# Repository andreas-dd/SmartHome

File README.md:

# SmartHome

## [HB-UNI-Sen-CAP-MOIST-Complete](HB-UNI-Sen-CAP-MOIST-Complete)
Ein kompakter Bodenfeuchtesensor komplett auf einer einzigen Platine inkl. kleinem Gehäuse.

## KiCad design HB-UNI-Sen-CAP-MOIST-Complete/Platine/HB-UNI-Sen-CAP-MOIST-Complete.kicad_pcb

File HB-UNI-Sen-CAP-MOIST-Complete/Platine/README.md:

# Platine und Schaltung

Hier findet sich das KiCad Projekt.
Die Batteriekontakte sind [Keystone Electronics 92](https://www.conrad.de/de/p/keystone-electronics-92-einzelkontakt-1x-mignon-aa-a-cr-2-durchsteckmontage-tht-b-x-h-12-mm-x-15-mm-651036.html).
Das Funkmodem ist ein Modul von [EByte](https://www.amazon.de/dp/B0BRZTSYPM?ref=ppx_yo2ov_dt_b_fed_asin_title&th=1).
Es kann ein zusätzlicher kapazitiver Sensor angeschlossen werden, ist im Sketch aber auskommentiert. Ebenfalls kann der Temperatursensor entfallen, dafür muss im Sketch in Zeile 15
```
   #define NO_DS18B20 
```
aktiviert werden.

## Bestückung
Beim ersten Exemplar habe ich nacheinander den Spannungsregler, dann den integrierten Sensor bestückt und geprüft. Danach den Prozessor verlötet sowie Fuses und Firmware programmiert. Zum Schluss das Funkmodem auflöten. Die nachfolgenden Platinen sind auf einen Rutsch mit Lötpaste und Heißluft bestückt worden, das Funkmodem nur an den markierten Kontakten mit dem Lötkolben. 

Die Antenne nicht vergessen, dafür einen 83mm langen Draht auf der Batterieseite bestücken und durch die [Antennenhalter](../Gehaeuse) fädeln:

# Schaltplan
der Schaltplan ist als [PDF verfügbar](HB-UNI-Sen-CAP-MOIST-Complete.pdf)

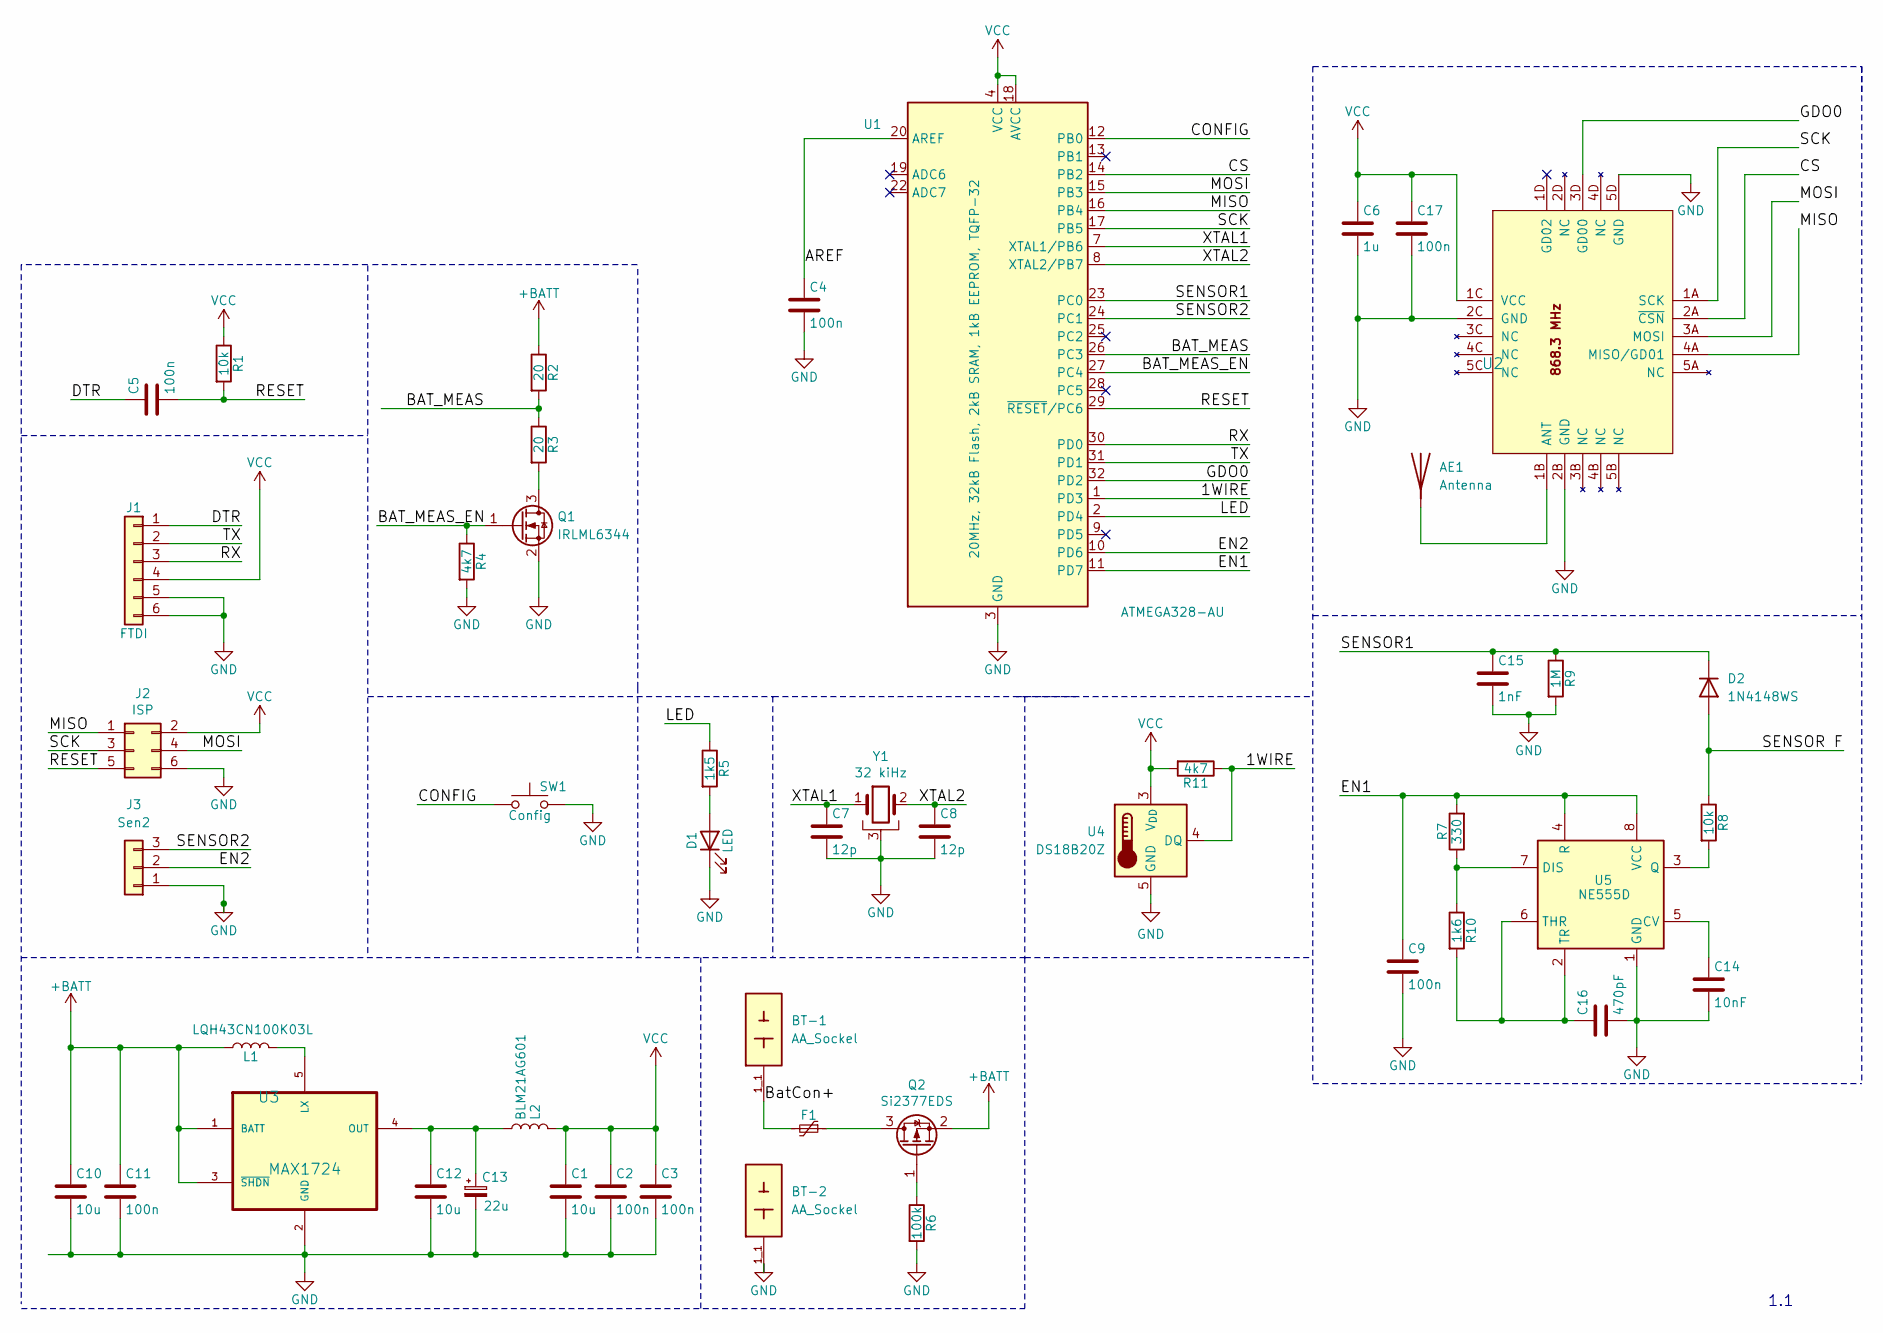
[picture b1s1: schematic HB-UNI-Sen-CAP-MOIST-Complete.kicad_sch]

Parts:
AE1: Antenna
BT-1, BT-2: AA_Sockel; AA Sockel; PARTREV N
C1, C10, C12: 10u; C_0805_2012Metric_Pad1.18x1.45mm_HandSolder
C2, C3, C4, C5, C9, C11, C17: 100n; C_0805_2012Metric_Pad1.18x1.45mm_HandSolder
C6: 1u; C_0805_2012Metric_Pad1.18x1.45mm_HandSolder
C7, C8: 12p; C_0805_2012Metric_Pad1.18x1.45mm_HandSolder
C13: 22u; CP_EIA-3528-21_Kemet-B_HandSolder
C14: 10nF; C_0805_2012Metric_Pad1.18x1.45mm_HandSolder
C15: 1nF; C_0805_2012Metric_Pad1.18x1.45mm_HandSolder
C16: 470pF; C_0805_2012Metric_Pad1.18x1.45mm_HandSolder
D1: LED; LED_0805_2012Metric_Pad1.15x1.40mm_HandSolder
D2: 1N4148WS; Diode_SOD-323
F1: PTC 6V/250mA; Sicherung_1206_HandSoldering
J1: FTDI; FTDI Arduino Connector
J2: ISP; ISP Connector_2x03_Pitch2.54mm_Tight_Fit
J3: Sen2; Connector Sensor CAP Moist Horizontal
L1: LQH43CN100K03L; Murata RF Inductors
L2: BLM21AG601; C_0805_2012Metric_Pad1.18x1.45mm_HandSolder
Q1: IRLML6344; SOT-23
Q2: Si2377EDS; SOT-23
R1, R8: 10k; R_0805_2012Metric_Pad1.20x1.40mm_HandSolder
R2, R3: 20; R_0805_2012Metric_Pad1.20x1.40mm_HandSolder
R4, R11: 4k7; R_0805_2012Metric_Pad1.20x1.40mm_HandSolder
R5: 1k5; R_0805_2012Metric_Pad1.20x1.40mm_HandSolder
R6: 100k; R_0805_2012Metric_Pad1.20x1.40mm_HandSolder
R7: 330; R_0805_2012Metric_Pad1.20x1.40mm_HandSolder
R9: 1M; R_0805_2012Metric_Pad1.20x1.40mm_HandSolder
R10: 1k6; R_0805_2012Metric_Pad1.20x1.40mm_HandSolder
SW1: Config; SW_SPST_CK_RS282G05A3
U1: ATMEGA328-AU; TQFP-32_7x7mm_P0.8mm; LCSC C14877
U2: CC1101; eByte_E07-900MM10S
U3: MAX1724; SOT-23-5_HandSoldering
U4: DS18B20Z; SOIC-8_3.9x4.9mm_P1.27mm
U5: NE555D; SOIC-8_3.9x4.9mm_P1.27mm
Y1: 32 kiHz; Crystal_SMD_MicroCrystal_MS3V-T1R

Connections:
+BATT: C10.1, C11.1, L1.2, Q2.2 (S), R2.1, U3.1 (BATT), U3.3 (~SHDN)
/1WIRE: R11.1, U1.1 (PD3), U4.4 (DQ)
/AREF: C4.1, U1.20 (AREF)
/BAT_MEAS: R2.2, R3.1, U1.26 (PC3)
/BAT_MEAS_EN: Q1.1 (G), R4.1, U1.27 (PC4)
/BatCon+: BT-1.1_1, BT-1.1_2, F1.2
/CONFIG: SW1.1, U1.12 (PB0)
/CS: U1.14 (PB2), U2.2A (~CSN)
/DTR: C5.1, J1.1
/EN1: C9.1, R7.2, U1.11 (PD7), U5.4 (R), U5.8 (VCC)
/EN2: J3.2, U1.10 (PD6)
/GDO0: U1.32 (PD2), U2.3D (GD00)
/LED: R5.1, U1.2 (PD4)
/MISO: J2.1, U1.16 (PB4), U2.4A (MISO/GD01)
/MOSI: J2.4, U1.15 (PB3), U2.3A (MOSI)
/RESET: C5.2, J2.5, R1.2, U1.29 (~RESET/PC6)
/RX: J1.3, U1.30 (PD0)
/SCK: J2.3, U1.17 (PB5), U2.1A (SCK)
/SENSOR1: C15.1, D2.1 (K), R9.1, U1.23 (PC0)
/SENSOR2: J3.3, U1.24 (PC1)
/SENSOR F: D2.2 (A), R8.1
/TX: J1.2, U1.31 (PD1)
/XTAL1: C7.1, U1.7 (XTAL1/PB6), Y1.1
/XTAL2: C8.1, U1.8 (XTAL2/PB7), Y1.2
GND: BT-2.1_1, BT-2.1_2, C1.2, C2.2, C3.2, C4.2, C6.2, C7.2, C8.2, C9.2, C10.2, C11.2, C12.2, C13.2, C14.2, C15.2, C16.2, C17.2, D1.1 (K), J1.5, J1.6, J2.6, J3.1, Q1.2 (S), R4.2, R6.2, R9.2, SW1.2, U1.3 (GND), U1.5 (GND), U1.21 (GND), U2.2B (GND), U2.2C (GND), U2.5D (GND), U3.2 (GND), U4.5 (GND), U5.1 (GND), Y1.3
unnamed: AE1.1, U2.1B (ANT)
unnamed: D1.2 (A), R5.2
unnamed: Q1.3 (D), R3.2
unnamed: F1.1, Q2.3 (D)
unnamed: Q2.1 (G), R6.1
unnamed: L1.1, U3.5 (LX)
unnamed: C12.1, C13.1, L2.1, U3.4 (OUT)
unnamed: C14.1, U5.5 (CV)
unnamed: R7.1, R10.1, U5.7 (DIS)
unnamed: R8.2, U5.3 (Q)
unnamed: C16.1, R10.2, U5.2 (TR), U5.6 (THR)
VCC: C1.1, C2.1, C3.1, C6.1, C17.1, J1.4, J2.2, L2.2, R1.1, R11.2, U1.4 (VCC), U1.6 (VCC), U1.18 (AVCC), U2.1C (VCC), U4.3 (V_{DD})

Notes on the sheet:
1.1

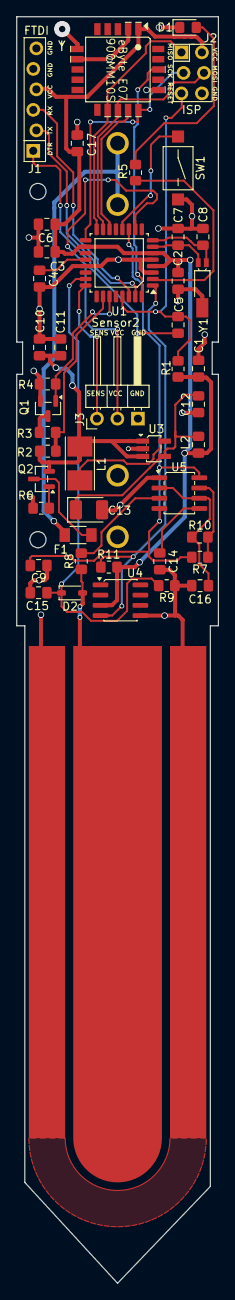
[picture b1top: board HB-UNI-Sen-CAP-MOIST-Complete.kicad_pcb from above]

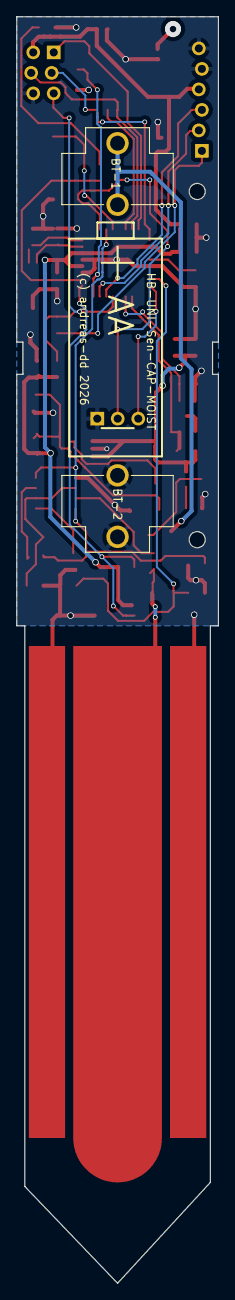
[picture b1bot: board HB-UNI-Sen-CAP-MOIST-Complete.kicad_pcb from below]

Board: 2 copper layers, 25.0 x 157.0 mm, 47 parts (2 on the bottom side), 36 nets.

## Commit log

2026-03-24 Initiale Version

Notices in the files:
HB-UNI-Sen-CAP-MOIST-Complete/Platine/HB-UNI-Sen-CAP-MOIST-Complete.kicad_pcb:
License: CC BY-NC-SA
parts and their libraries:
Copyright: (c) Andreas Lotze 2025
